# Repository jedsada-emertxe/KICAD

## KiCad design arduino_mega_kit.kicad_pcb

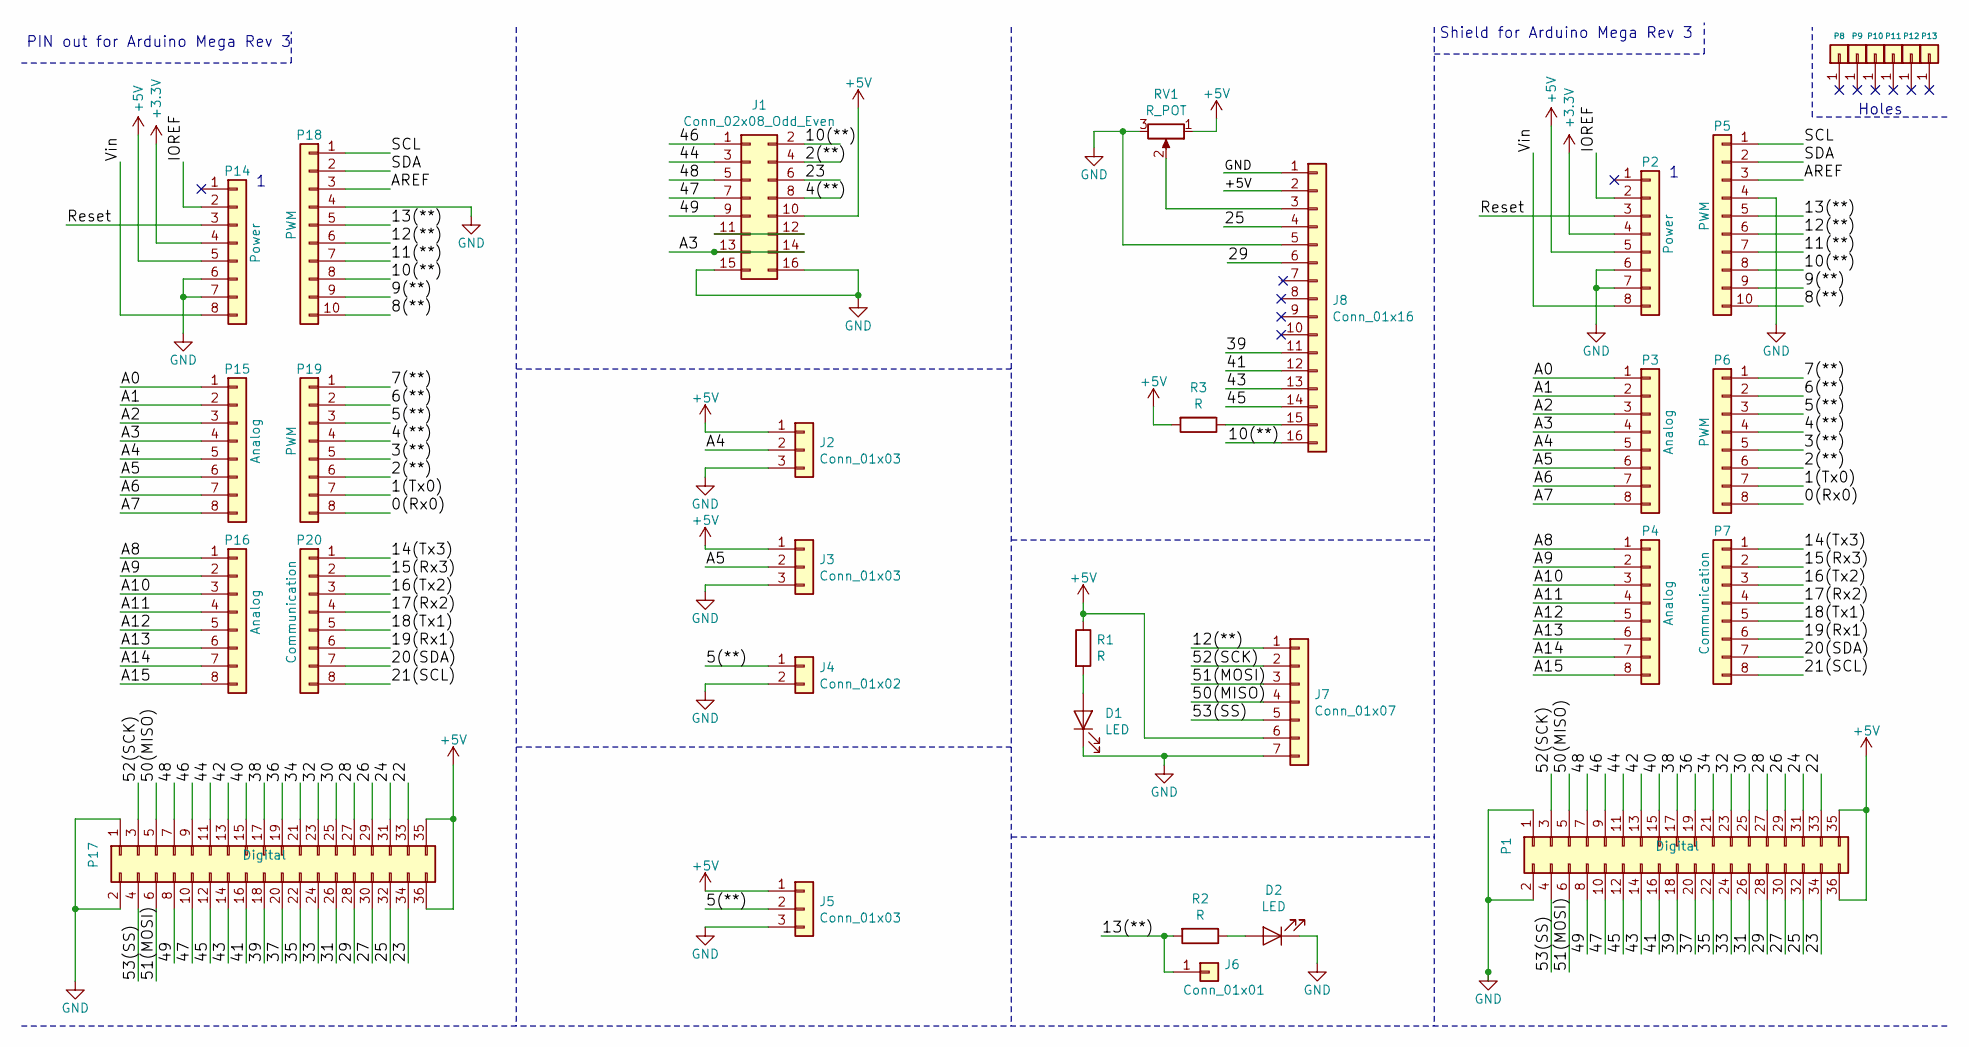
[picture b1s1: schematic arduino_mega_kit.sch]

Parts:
D1, D2: LED; LED_D3.0mm
J1: Conn_02x08_Odd_Even; IDC-Header_2x08_P2.54mm_Vertical
J2, J3, J5: Conn_01x03; PinHeader_1x03_P2.54mm_Vertical
J4: Conn_01x02; PinHeader_1x02_P2.54mm_Vertical
J6: Conn_01x01; PinHeader_1x01_P2.54mm_Vertical
J7: Conn_01x07; PinSocket_1x07_P2.54mm_Vertical
J8: Conn_01x16; PinHeader_1x16_P2.54mm_Vertical
P1: Digital; PinSocket_2x18_P2.54mm_Vertical
P2, P14: Power; PinHeader_1x08_P2.54mm_Vertical
P3, P4, P15, P16: Analog; PinHeader_1x08_P2.54mm_Vertical
P5, P18: PWM; PinHeader_1x10_P2.54mm_Vertical
P6, P19: PWM; PinHeader_1x08_P2.54mm_Vertical
P7, P20: Communication; PinHeader_1x08_P2.54mm_Vertical
P8, P9, P10, P11, P12, P13: CONN_01X01; PinHeader_1x01_P2.54mm_Vertical
P17: Digital; PinHeader_2x18_P2.54mm_Vertical
R1, R2, R3: R; R_Axial_DIN0207_L6.3mm_D2.5mm_P7.62mm_Horizontal
RV1: R_POT; Potentiometer_ACP_CA6-H2,5_Horizontal

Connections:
+3V3: P2.4, P14.4
+5V: J1.10, J2.1, J3.1, J5.1, J7.6, J8.2, P1.35, P1.36, P2.5, P14.5, P17.35, P17.36, R1.1, R3.2, RV1.1
/0(Rx0): P6.8, P19.8
/1(Tx0): P6.7, P19.7
/2(**): J1.4, P6.6, P19.6
/3(**): P6.5, P19.5
/4(**): J1.8, P6.4, P19.4
/5(**): J4.1, J5.2, P6.3, P19.3
/6(**): P6.2, P19.2
/7(**): P6.1, P19.1
/8(**): P5.10, P18.10
/9(**): P5.9, P18.9
/10(**): J1.2, J8.16, P5.8, P18.8
/11(**): P5.7, P18.7
/12(**): J7.1, P5.6, P18.6
/13(**): J6.1, P5.5, P18.5, R2.2
/14(Tx3): P7.1, P20.1
/15(Rx3): P7.2, P20.2
/16(Tx2): P7.3, P20.3
/17(Rx2): P7.4, P20.4
/18(Tx1): P7.5, P20.5
/19(Rx1): P7.6, P20.6
/20(SDA): P7.7, P20.7
/21(SCL): P7.8, P20.8
/22: P1.33, P17.33
/23: J1.6, P1.34, P17.34
/24: P1.31, P17.31
/25: J8.4, P1.32, P17.32
/26: P1.29, P17.29
/27: P1.30, P17.30
/28: P1.27, P17.27
/29: J8.6, P1.28, P17.28
/30: P1.25, P17.25
/31: P1.26, P17.26
/32: P1.23, P17.23
/33: P1.24, P17.24
/34: P1.21, P17.21
/35: P1.22, P17.22
/36: P1.19, P17.19
/37: P1.20, P17.20
/38: P1.17, P17.17
/39: J8.11, P1.18, P17.18
/40: P1.15, P17.15
/41: J8.12, P1.16, P17.16
/42: P1.13, P17.13
/43: J8.13, P1.14, P17.14
/44: J1.3, P1.11, P17.11
/45: J8.14, P1.12, P17.12
/46: J1.1, P1.9, P17.9
/47: J1.7, P1.10, P17.10
/48: J1.5, P1.7, P17.7
/49: J1.9, P1.8, P17.8
/50(MISO): J7.4, P1.5, P17.5
/51(MOSI): J7.3, P1.6, P17.6
/52(SCK): J7.2, P1.3, P17.3
/53(SS): J7.5, P1.4, P17.4
/A0: P3.1, P15.1
/A1: P3.2, P15.2
/A2: P3.3, P15.3
/A3: J1.13, J1.14, P3.4, P15.4
/A4: J2.2, P3.5, P15.5
/A5: J3.2, P3.6, P15.6
/A6: P3.7, P15.7
/A7: P3.8, P15.8
/A8: P4.1, P16.1
/A9: P4.2, P16.2
/A10: P4.3, P16.3
/A11: P4.4, P16.4
/A12: P4.5, P16.5
/A13: P4.6, P16.6
/A14: P4.7, P16.7
/A15: P4.8, P16.8
/AREF: P5.3, P18.3
/IOREF: P2.2, P14.2
/Reset: P2.3, P14.3
/SCL: P5.1, P18.1
/SDA: P5.2, P18.2
/Vin: P2.8, P14.8
GND: D1.1 (K), D2.1 (K), J1.15, J1.16, J2.3, J3.3, J4.2, J5.3, J7.7, J8.1, J8.5, P1.1, P1.2, P2.6, P2.7, P5.4, P14.6, P14.7, P17.1, P17.2, P18.4, RV1.3
unnamed: D1.2 (A), R1.2
unnamed: D2.2 (A), R2.1
unnamed: J1.11, J1.12
unnamed: J8.3, RV1.2
unnamed: J8.15, R3.1

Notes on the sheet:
Shield for Arduino Mega Rev 3
Holes
PIN out for Arduino Mega Rev 3

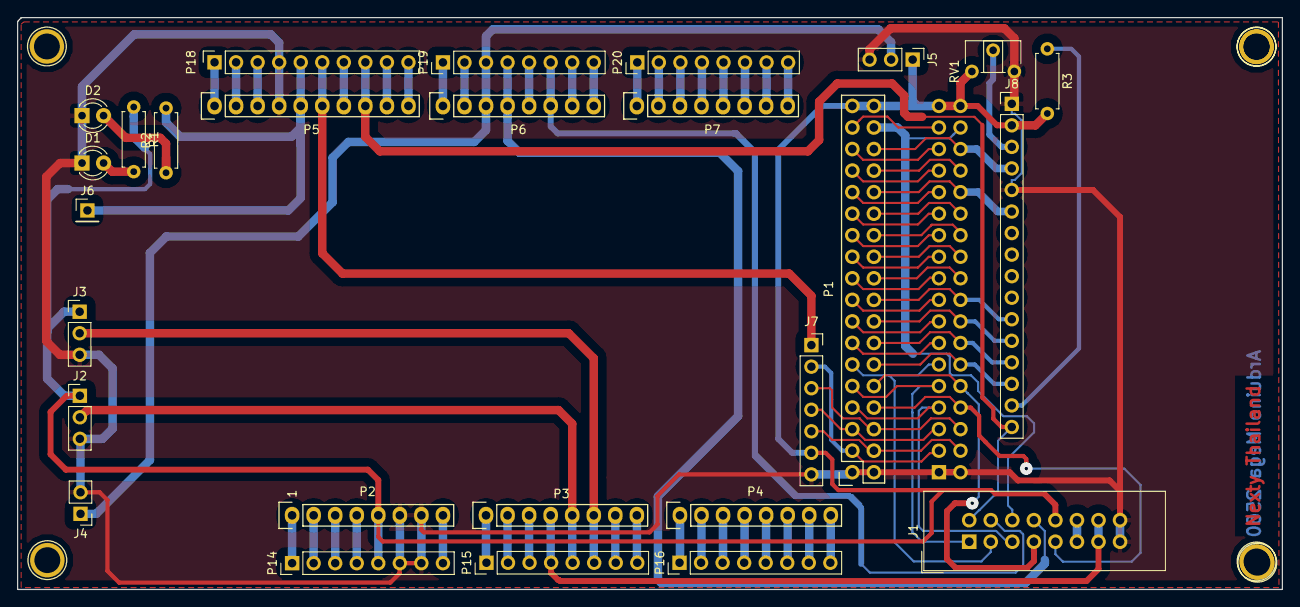
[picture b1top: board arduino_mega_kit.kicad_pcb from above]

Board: 2 copper layers, 149.1 x 67.4 mm, 34 parts (1 on the bottom side), 84 nets.

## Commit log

2018-11-11 Create Arduino_Mega
